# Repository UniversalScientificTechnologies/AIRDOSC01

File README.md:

# AIRDOSC01B - AIRDOS dosimeter with scintillator-based sensor
*AIRDOS-C Scintillation detector of ionizing radiation with a full production specification available. The device can be further modified according to specific requirements. The character of its construction makes it suitable for placement into UAVs.*

**Technical parameters are the following:**

* Detection element: scintillating crystal integrated with [SiPM](https://en.wikipedia.org/wiki/Silicon_photomultiplier)
* More than 90 days of autonomous operation powered by a lithium battery
* Data memory: SD card
* Data logs contain the energy and time of each event
* Logging periodicity: 10 s (dead time 2 s)
* Time resolution: 20 us
* Accuracy of event’s time: 500 ns
* Dimensions: 57 x 107 x 167 mm
* Mass in operating condition (including batteries) 1 kg
* Open-source HW and SW
* Device status indicator: LED on panel
* Airborne GPS parameters (measurement altitude verified up to 36km a.m.s.l.)

Since 2023, AIRDOSC has been discontinued. Please consider a newer [UST dosimeter series](https://www.ust.cz/UST-dosimeters/). 

**Device block diagram**

**Production data of electronic modules**

* [STEPUPDC02A](https://github.com/mlab-modules/STEPUPDC02)
* [SIPM02C](https://github.com/mlab-modules/SIPM02) known as "AIRDOSC01A_PCB01C"
* [PCRD06A](https://github.com/mlab-modules/PCRD06)
* [GPS01B](https://www.mlab.cz/module/GPS01B)
* [DATALOGGER01A](http://mlab.cz/module/DATALOGGER01A)

Relevant scientific papers

* [CHARACTERISATION OF AIRDOS-C DETECTOR FOR MEASUREMENT OF HIGH-ENERGY EVENTS IN THE ATMOSPHERE](https://academic.oup.com/rpd/article-abstract/198/9-11/604/6672998?redirectedFrom=fulltext&login=false)

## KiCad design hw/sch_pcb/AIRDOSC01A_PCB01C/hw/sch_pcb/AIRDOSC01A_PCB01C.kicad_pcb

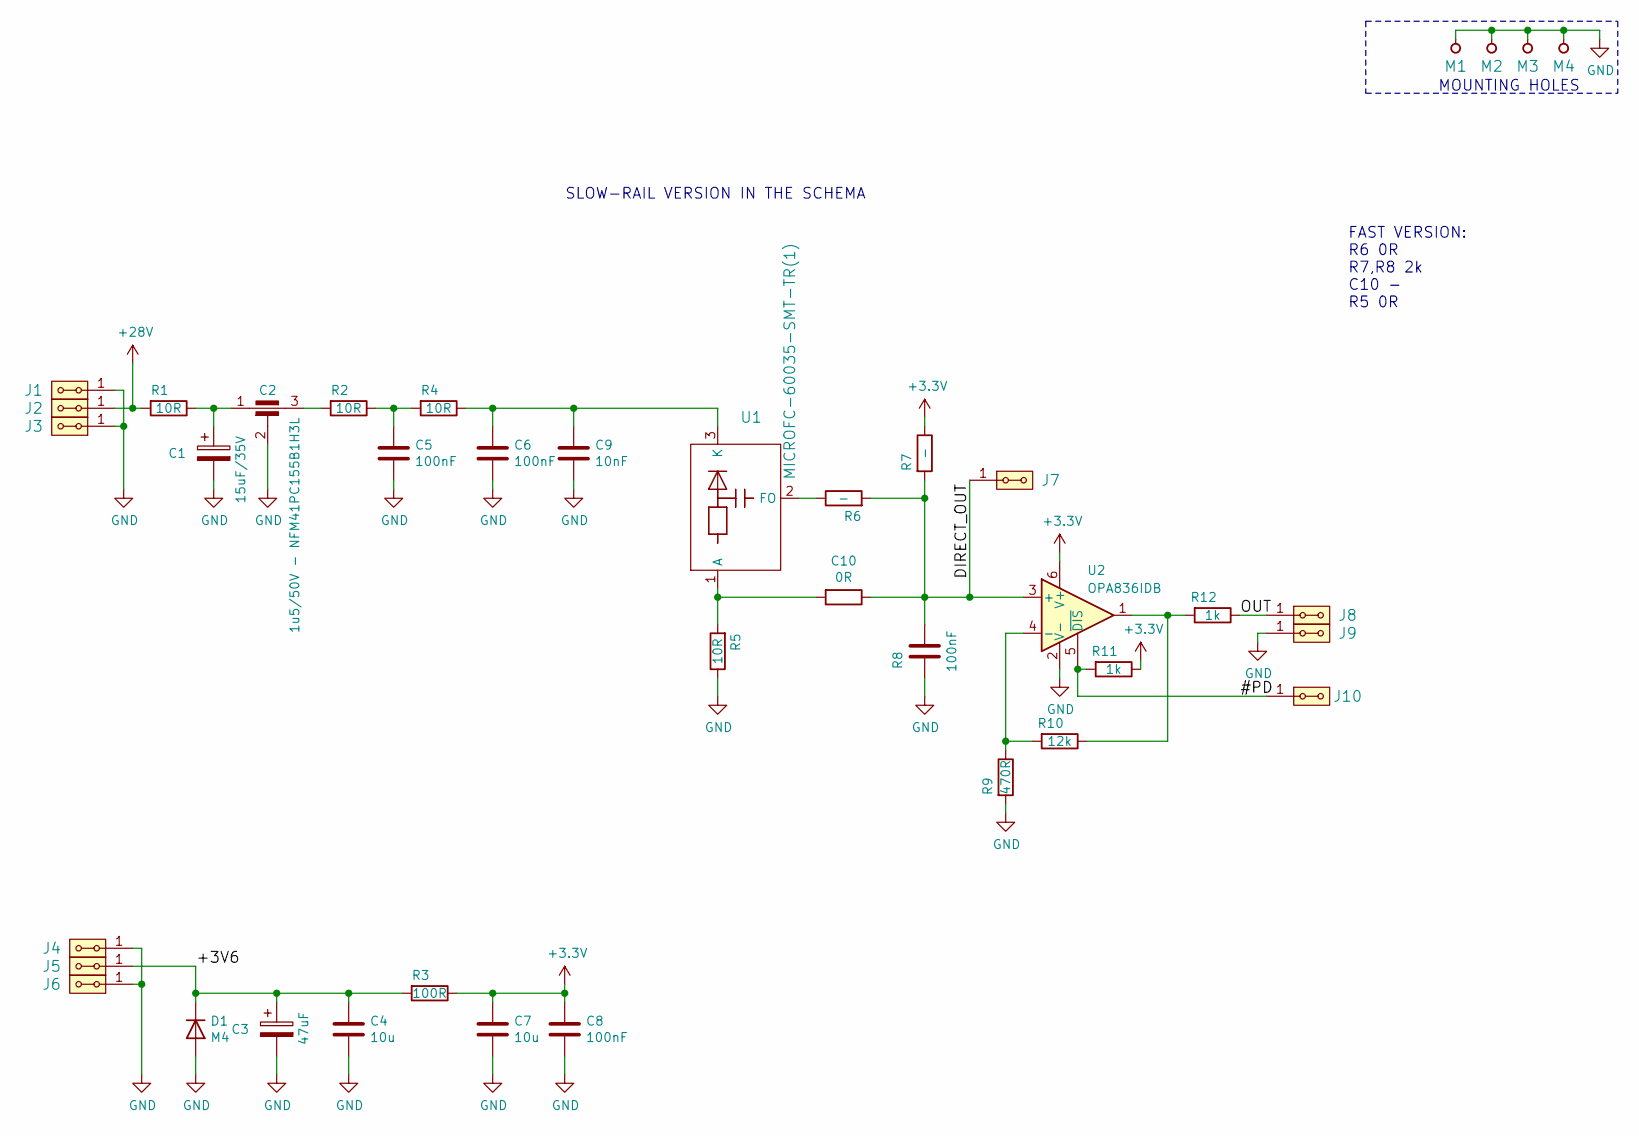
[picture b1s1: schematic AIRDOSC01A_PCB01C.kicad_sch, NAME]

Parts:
C1: 15uF/35V; TantalC_SizeC_Reflow
C2: 1u5/50V - NFM41PC155B1H3L; FIR_1806
C3: 47uF; TantalC_SizeC_Reflow
C4, C7: 10u; SMD-0805
C5, C6, C8: 100nF; SMD-0805
C9: 10nF; SMD-0805
C10: 0R; SMD-0805
D1: M4; Diode-SMA_Standard
J1, J2, J3, J4, J5, J6, J7, J8, J9, J10: HEADER_2x01_PARALLEL; Straight_2x01
M1, M2, M3, M4: HOLE; MountingHole_3mm
R1, R2, R4, R5: 10R; SMD-0805
R3: 100R; SMD-0805
R6, R7: -; SMD-0805
R8: 100nF; SMD-0805
R9: 470R; SMD-0805
R10: 12k; SMD-0805
R11, R12: 1k; SMD-0805
U1: MICROFC-60035-SMT-TR(1); MicroFC−60035−SMT
U2: OPA836IDB; SOT-23-6

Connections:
+3V3: C7.1, C8.1, R3.1, R7.1, R11.1, U2.6 (V+)
+28V: J2.1, J2.2, R1.2
/#PD: J10.1, J10.2, R11.2, U2.5 (~DIS)
/+3V6: C3.1, C4.1, D1.1 (K), J5.1, J5.2, R3.2
/DIRECT_OUT: C10.1, J7.1, J7.2, R6.2, R7.2, R8.1, U2.3 (+)
/OUT: J8.1, J8.2, R12.1
GND: C1.2, C2.2, C3.2, C4.2, C5.2, C6.2, C7.2, C8.2, C9.2, D1.2 (A), J1.1, J1.2, J3.1, J3.2, J4.1, J4.2, J6.1, J6.2, J9.1, J9.2, M1.1, M2.1, M3.1, M4.1, R5.1, R8.2, R9.2, U2.2 (V-)
unnamed: C1.1, C2.1, R1.1
unnamed: C2.3, R2.2
unnamed: C5.1, R2.1, R4.2
unnamed: C6.1, C9.1, R4.1, U1.3 (K)
unnamed: C10.2, R5.2, U1.1 (A)
unnamed: R6.1, U1.2 (FO)
unnamed: R10.1, R12.2, U2.1
unnamed: R9.1, R10.2, U2.4 (-)

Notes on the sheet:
SLOW-RAIL VERSION IN THE SCHEMA
FAST VERSION: R6 0R R7,R8 2k C10 - R5 0R
MOUNTING HOLES

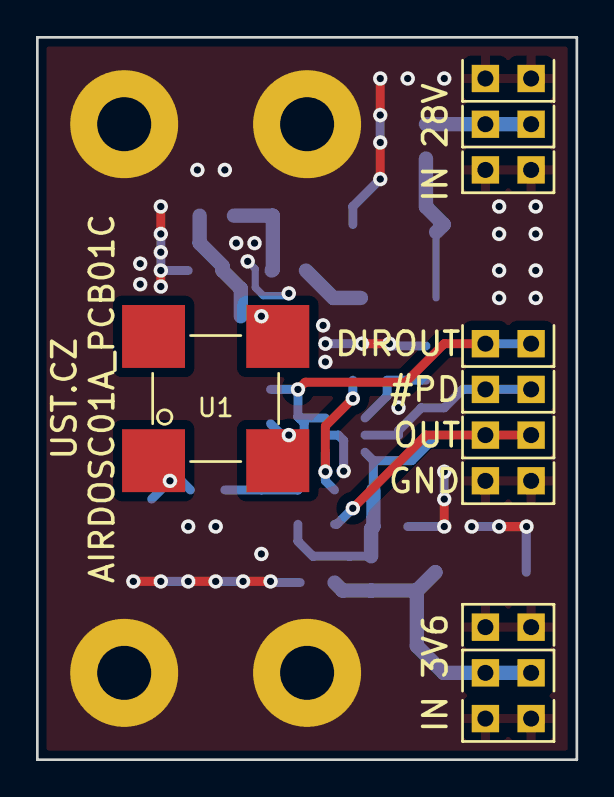
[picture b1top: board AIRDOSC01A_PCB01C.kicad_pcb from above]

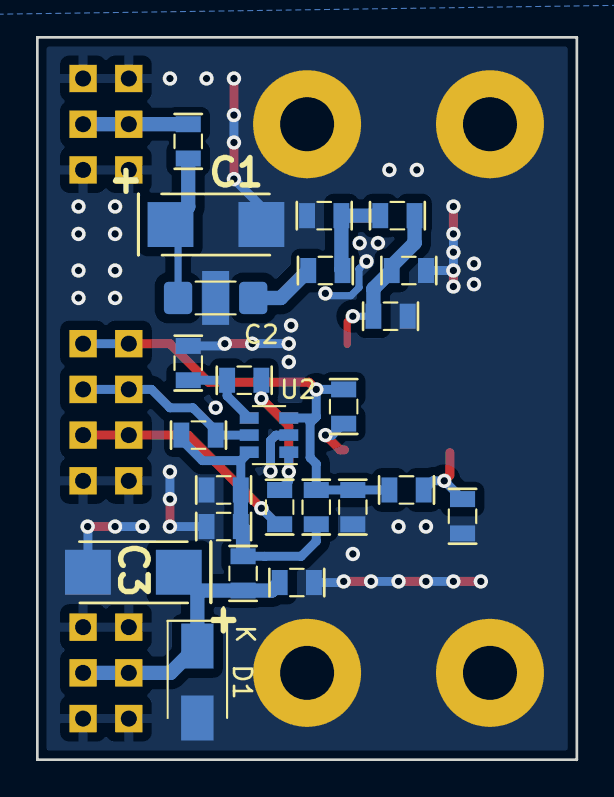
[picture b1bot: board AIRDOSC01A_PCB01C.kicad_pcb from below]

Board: 2 copper layers, 30.0 x 40.1 mm, 39 parts (24 on the bottom side), 15 nets.

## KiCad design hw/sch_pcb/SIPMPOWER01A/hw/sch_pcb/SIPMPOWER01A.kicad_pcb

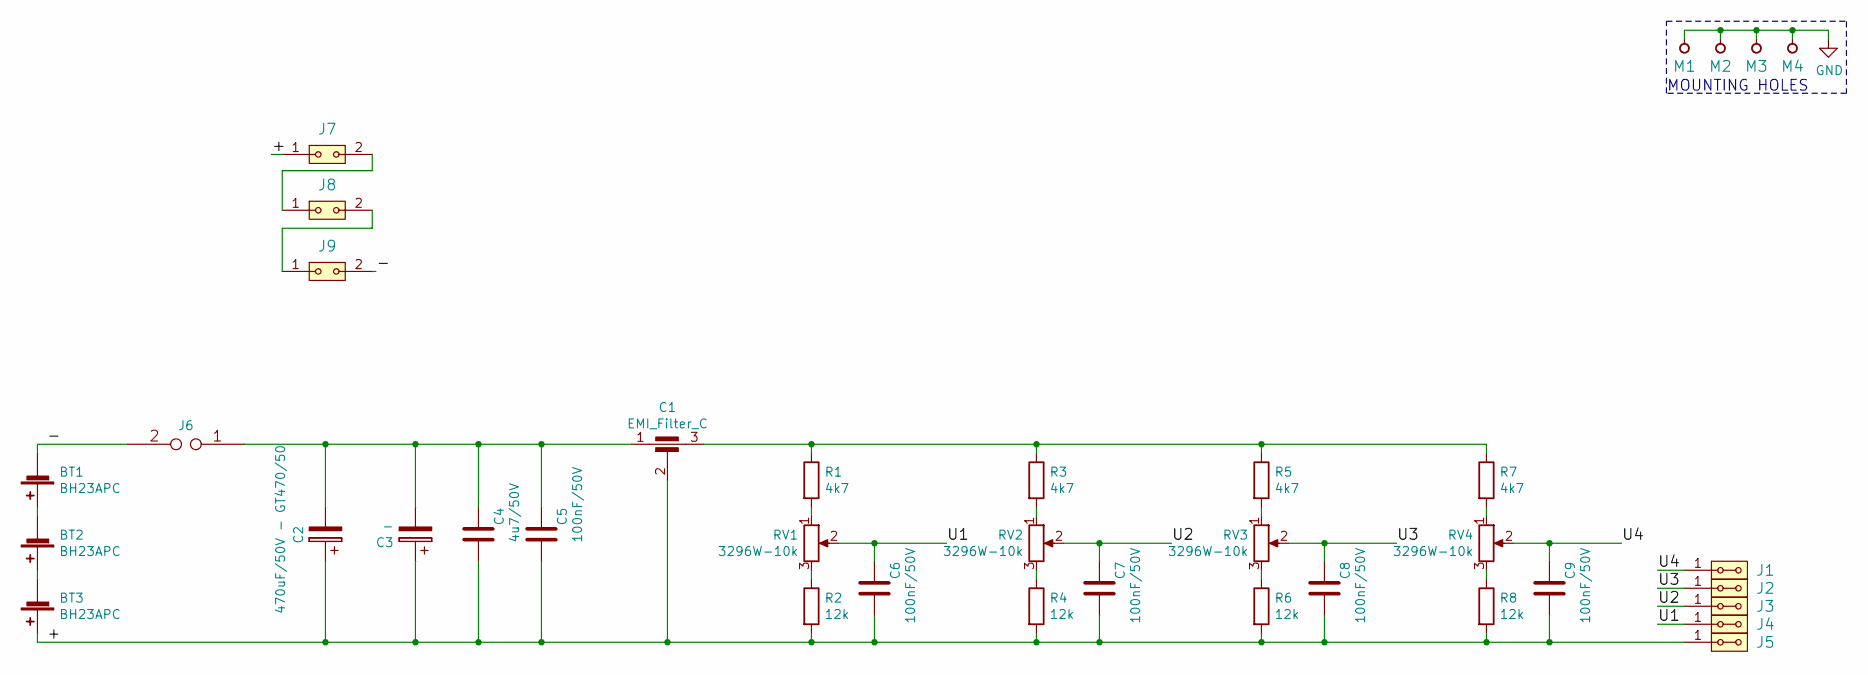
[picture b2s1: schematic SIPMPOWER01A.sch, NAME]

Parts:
BT1, BT2, BT3: BH23APC
C1: EMI_Filter_C; FIR_1806
C2: 470uF/50V - GT470/50; CP_Radial_D10.0mm_P5.00mm
C3: -; TantalC_SizeC_Reflow
C4: 4u7/50V; SMD-0805
C5, C6, C7, C8, C9: 100nF/50V; SMD-0805
J1, J2, J3, J4, J5: HEADER_2x01_PARALLEL; Straight_2x01
J6: JUMP2_2x1; Straight_1x02
J7, J8, J9: HEADER_2x01; Straight_1x02
M1, M2, M3, M4: HOLE; MountingHole_3mm
R1, R3, R5, R7: 4k7; SMD-0805
R2, R4, R6, R8: 12k; SMD-0805
RV1, RV2, RV3, RV4: 3296W-10k; Potentiometer_Bourns_3296W_Vertical

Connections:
/+: BT3.1 (+), C1.2, C2.1, C3.1, C4.2, C5.2, C6.2, C7.2, C8.2, C9.2, J5.1, J5.2, J7.1, R2.2, R4.2, R6.2, R8.2
/-: BT1.2 (-), J6.2, J9.2
/U1: C6.1, J4.1, J4.2, RV1.2
/U2: C7.1, J3.1, J3.2, RV2.2
/U3: C8.1, J2.1, J2.2, RV3.2
/U4: C9.1, J1.1, J1.2, RV4.2
GND: M1.1, M2.1, M3.1, M4.1
unnamed: BT1.1 (+), BT2.2 (-)
unnamed: BT2.1 (+), BT3.2 (-)
unnamed: C1.1, C2.2, C3.2, C4.1, C5.1, J6.1
unnamed: C1.3, R1.1, R3.1, R5.1, R7.1
unnamed: J7.2, J8.1
unnamed: J8.2, J9.1
unnamed: R1.2, RV1.1
unnamed: R2.1, RV1.3
unnamed: R3.2, RV2.1
unnamed: R4.1, RV2.3
unnamed: R5.2, RV3.1
unnamed: R6.1, RV3.3
unnamed: R7.2, RV4.1
unnamed: R8.1, RV4.3

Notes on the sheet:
MOUNTING HOLES

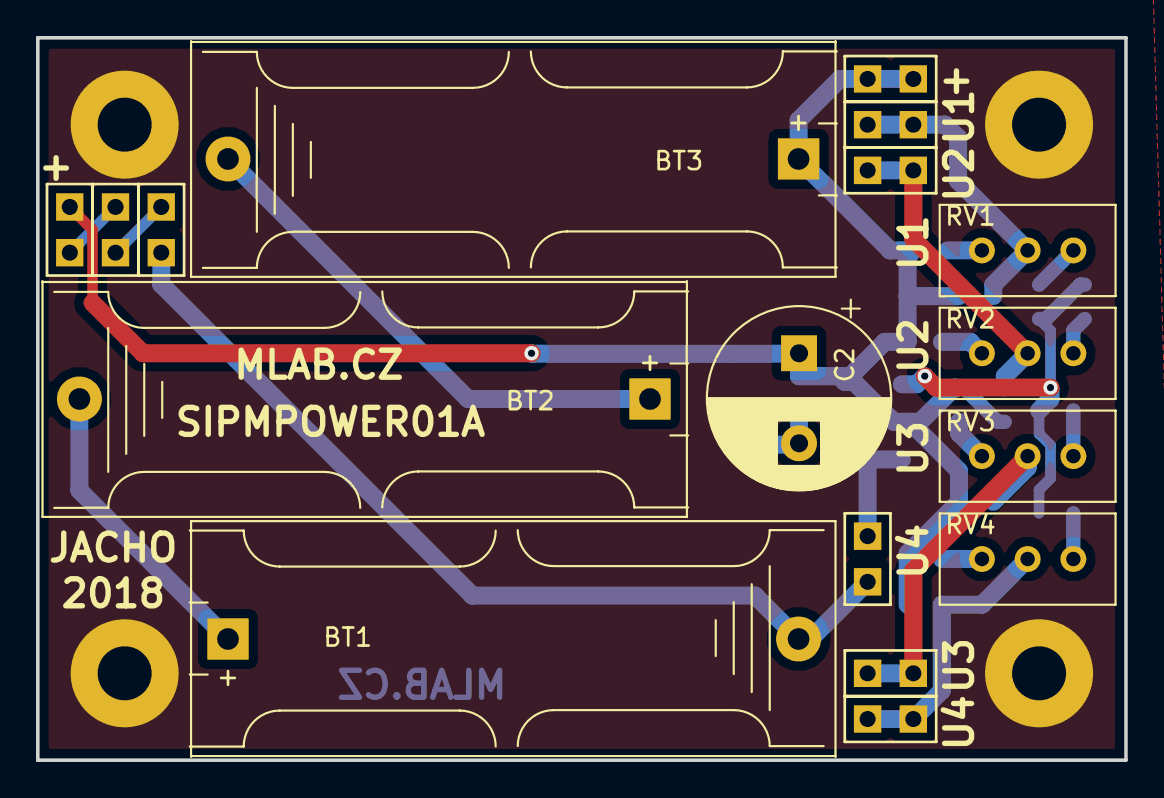
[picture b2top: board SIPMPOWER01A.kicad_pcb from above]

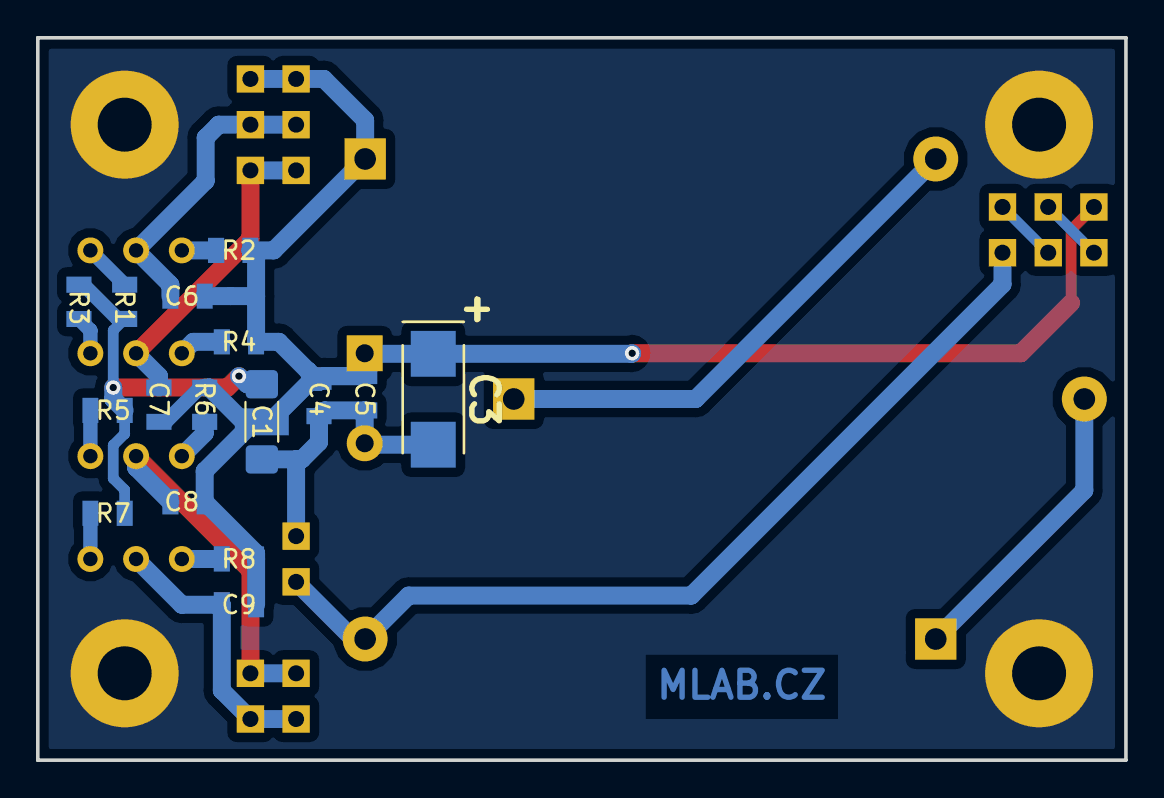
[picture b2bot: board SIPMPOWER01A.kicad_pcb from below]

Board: 2 copper layers, 60.5 x 40.1 mm, 37 parts (16 on the bottom side), 21 nets.

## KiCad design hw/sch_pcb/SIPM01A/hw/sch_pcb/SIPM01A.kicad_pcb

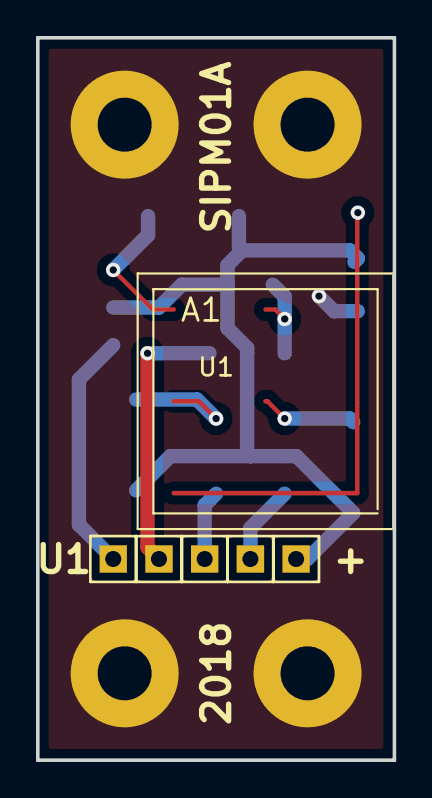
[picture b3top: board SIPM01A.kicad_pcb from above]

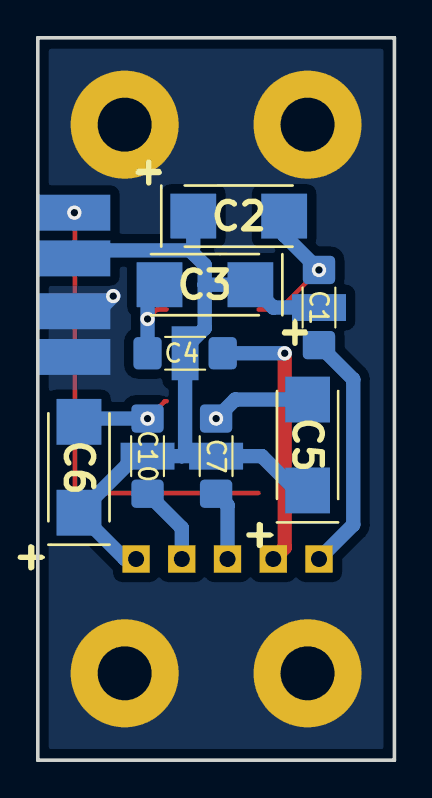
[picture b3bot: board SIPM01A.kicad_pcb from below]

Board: 2 copper layers, 19.8 x 40.1 mm, 20 parts (10 on the bottom side), 11 nets.

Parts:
C1, C4, C7, C10: 1u5/50V - NFM41PC155B1H3L; FIR_1806
C2, C3, C5, C6: CP; TantalC_SizeC_Reflow
J1, J2, J3, J4, J7: HEADER_1x01; Straight_1x01
J5, J6: CONN_2; SMD_1_2_4x2
M1, M2, M3, M4: HOLE; MountingHole_3mm
U1: ARRAYC-60035-4P-BGA; ArrayC-60035-4P-BGA

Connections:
/+: C1.2, C2.1, C3.1, C4.2, C5.1, C6.1, C7.2, C10.2, J5.2, J7.1
/K: J5.1, U1.A3, U1.B3, U1.C1, U1.C2, U1.C3
/U1: C1.3, C2.2, U1.A1
/U1in: C1.1, J1.1
/U2: C3.2, C4.3, U1.A2
/U2in: C4.1, J2.1
/U3: C5.2, C7.3, U1.B1
/U3in: C7.1, J3.1
/U4: C6.2, C10.3, U1.B2
/U4in: C10.1, J4.1
GND: J6.1, J6.2, M1.1, M2.1, M3.1, M4.1

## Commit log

2018-09-28 Návrh PCB
2018-09-29 Edit
2018-09-30 Modifications
2018-10-11 Krabička pro zatemnění krystalu.
2018-10-12 Drzak PCRD
2018-10-18 Rozříšení držáku pro krystal.
2018-10-22 Adding new labels.
2018-10-22 Renaming files to correct name according to page size.
2018-12-03 Nový PCB pod SIPM
2018-12-04 Krabička pro krystal
2018-12-10 schema
2018-12-10 Editace dokumentace
2018-12-10 změna názvu obrázku
2018-12-14 Updated link in QRcode.
2018-12-21 new photo
2019-01-03 Odebrani nevhodneho drzaku
2019-01-14 Doplneni licence a gitignore
2019-01-29 Update front photo.
2019-01-30 Odstraneni starych fotek
2019-02-08 PCB01A
2019-03-08 List bullet removed
2019-04-11 Smazání starých souborů
2019-05-16 generovani gkodu
2019-07-18 Zmena parametru
2019-08-07 Edit 3D model
2020-06-12 holder for NaITl crystal
2021-02-11 Úprava pouzdra SiPM
2021-02-24 Přiřazení součástek
2021-03-14 holder for new crystal from Ukraine
2021-04-03 Úprava hodnot ve schématu.
2021-05-24 Add note about GPS limits.
2021-07-20 Edit PCB
2021-10-18 Improve documentation for PCB01 SiMP holder.
2021-10-18 Fix image path.
2021-11-03 figures for publication
2021-12-19 Fix disfunctional assembly.
2022-01-03 Change R10 from 6k8 to 12k
2022-04-02 Cleanup the documentation and move of designs to separate repositories #4 https://github.com/mlab-modules/SIPMPOWER01 https://github.com/mlab-modules/SIPM02
2022-04-02 Update documentation to recent version of used modules.
2022-04-02 Fix typo.
